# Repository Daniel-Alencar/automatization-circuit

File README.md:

# Circuito para gerenciamento de tomadas de forma programada
Sistema de tomada inteligente que controla até duas saídas de energia. Nesse sistema o usuário poderia ligar ou desligar aparelhos de maneira remota por meio de um controle infravermelho. Além disso, o usuário pode ativar timers definindo um tempo específico para ligar ou desligar um aparelho. Como recurso adicional, o usuário pode configurar outros controles infravermelho para serem lidos e entendidos no sistema.

### Observação
Este repositório possui somente o esquemático do circuito.

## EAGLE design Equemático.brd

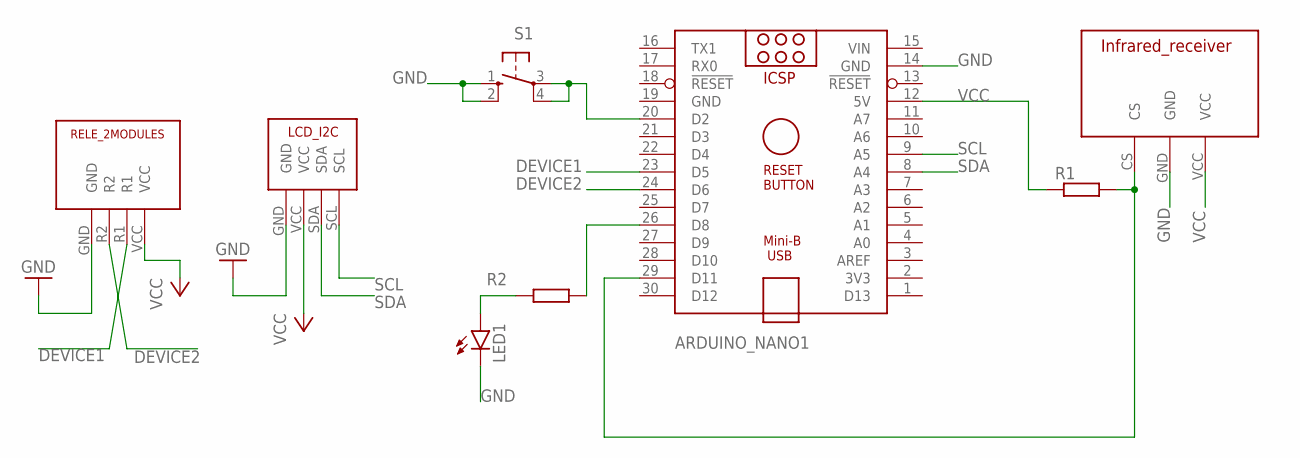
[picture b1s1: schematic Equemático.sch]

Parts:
ARDUINO_NANO1: ARDUINO_NANO
LED1: LED5MM
R1, R2: R-EU_0207/10; 0207/10
S1: 10-XX; B3F-10XX
U$1: INFRARED_RECEIVER; INFRARED_RECEIVER_FOOTPRINT
U$6: RELE_2MODULES; RELE_2MODULES_FOOTPRINT
U$10: LCD_I2C; LCD_I2C_FOOTPRINT

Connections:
DEVICE1: ARDUINO_NANO1.23 (D5), U$6.R1
DEVICE2: ARDUINO_NANO1.24 (D6), U$6.R2
GND: ARDUINO_NANO1.14 (GND), ARDUINO_NANO1.19 (GND), LED1.K (C), S1.1 (S), S1.2 (S1), U$1.GND, U$6.GND, U$10.GND
unnamed: ARDUINO_NANO1.26 (D8), R2.2
unnamed: LED1.A, R2.1
unnamed: ARDUINO_NANO1.29 (D11), R1.2, U$1.CS
unnamed: ARDUINO_NANO1.20 (D2), S1.3, S1.4 (P1)
SCL: ARDUINO_NANO1.9 (A5), U$10.SCL
SDA: ARDUINO_NANO1.8 (A4), U$10.SDA
VCC: ARDUINO_NANO1.12 (5V), R1.1, U$1.VCC, U$6.VCC, U$10.VCC
VIN: ARDUINO_NANO1.15 (VIN)

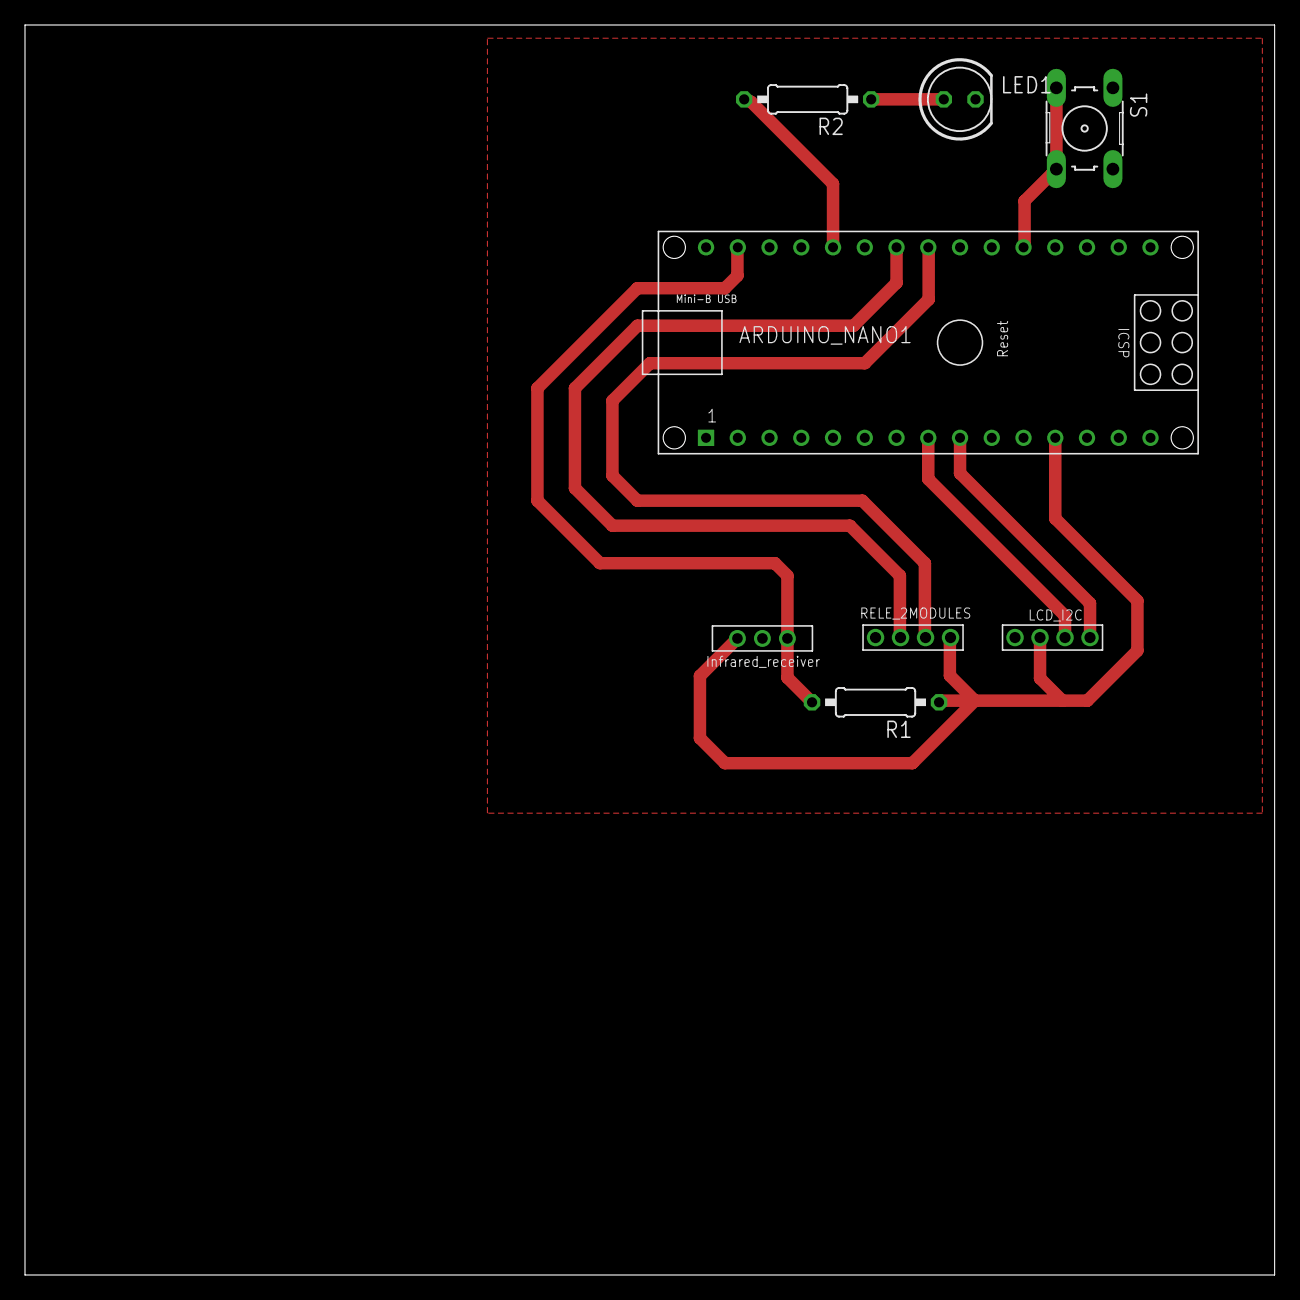
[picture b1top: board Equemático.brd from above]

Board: 2 copper layers, 100.0 x 100.0 mm, 8 parts (0 on the bottom side), 10 nets.

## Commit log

2025-03-27 added readme
